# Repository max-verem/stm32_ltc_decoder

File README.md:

# stm32_ltc_decoder

This device used for decoding LTC from VTRs or other sources. Output sent to CDC serial.

## used parts

### STM32 BluePill board

### RS485 module

Note: **R7** should be removed

### other
* 2N7000
* Jumper
* Prototyping PCB

## connection diagram

## output example

## working model

## notes

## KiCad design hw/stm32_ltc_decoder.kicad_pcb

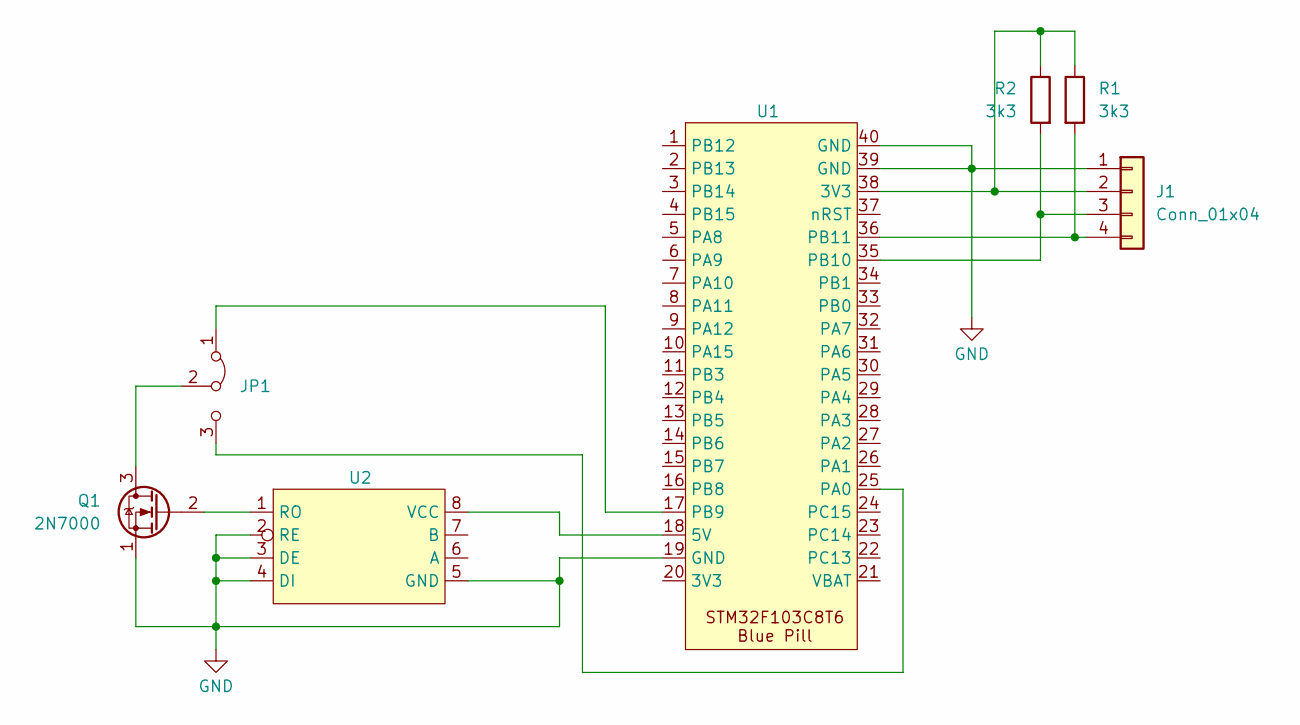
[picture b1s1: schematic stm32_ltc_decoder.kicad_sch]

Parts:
J1: Conn_01x04; PinHeader_1x04_P2.54mm_Vertical
JP1: Jumper_3_Bridged12; PinSocket_1x03_P2.54mm_Vertical
Q1: 2N7000; PinSocket_1x03_P2.54mm_Vertical
R1, R2: 3k3; R_Axial_DIN0207_L6.3mm_D2.5mm_P10.16mm_Horizontal
U1: BluePill (STM32F103C8T6)
U2: RS485_MODULE

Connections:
GND: J1.1, Q1.1 (S), U1.19 (GND), U1.39 (GND), U1.40 (GND), U2.2 (RE), U2.3 (DE), U2.4 (DI), U2.5 (GND)
unnamed: J1.2, R1.1, R2.1, U1.38 (3V3)
unnamed: J1.3, R2.2, U1.35 (PB10)
unnamed: J1.4, R1.2, U1.36 (PB11)
unnamed: JP1.1 (A), U1.17 (PB9)
unnamed: JP1.3 (B), U1.25 (PA0)
unnamed: JP1.2 (C), Q1.3 (D)
unnamed: Q1.2 (G), U2.1 (RO)
unnamed: U1.18 (5V), U2.8 (VCC)

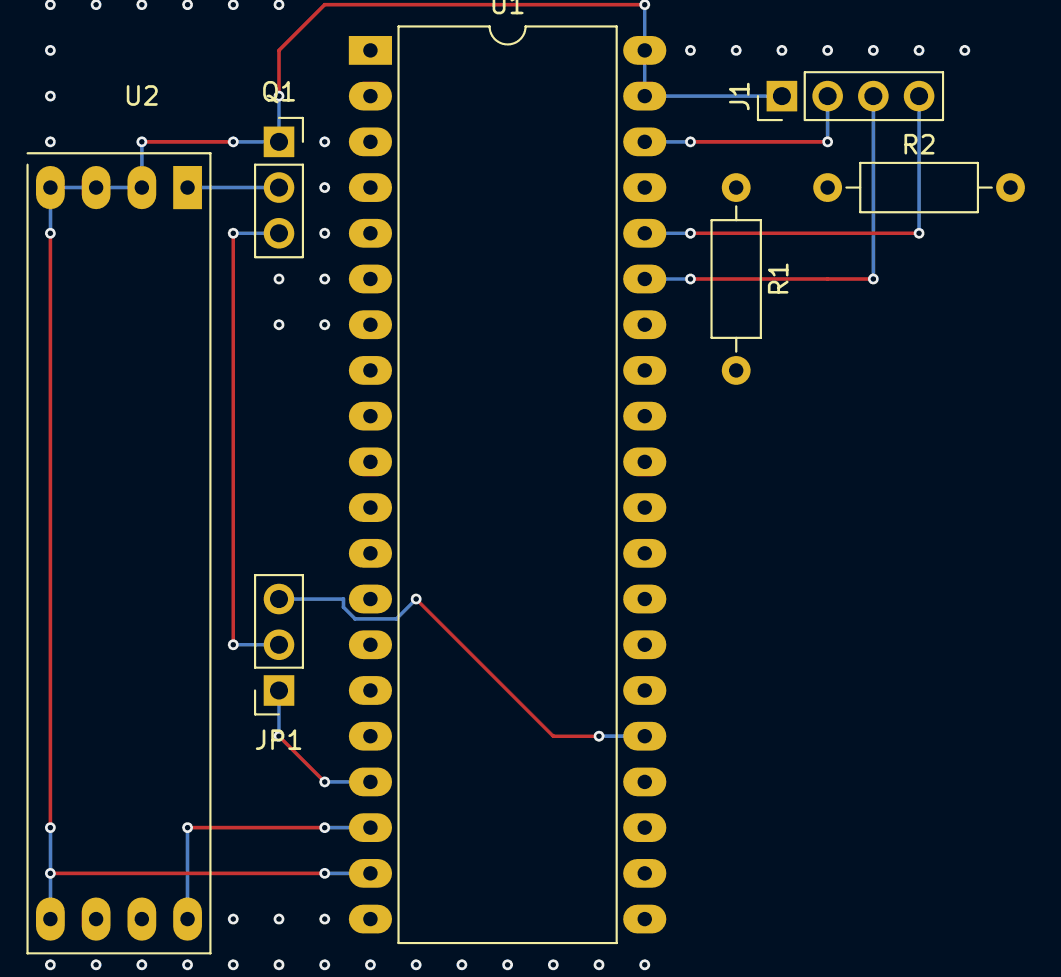
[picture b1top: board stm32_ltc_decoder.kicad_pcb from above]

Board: 2 copper layers, 7 parts (0 on the bottom side), 9 nets.

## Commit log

2024-12-31 Some photos added
2025-03-02 Schematic and source code updated
2025-03-09 Add padding to framebuffer bank/row/line
2025-03-09 Update schematic for connector porpose
